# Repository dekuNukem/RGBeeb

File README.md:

# Pimp My Beeb

How I built the **RGBeeb**, a BBC Micro inside a PC case.

With RGB Backlight, USB inputs, ATX PSU, and working full-height floppy drives.

[Click me for a short video!](https://www.youtube.com/watch?v=R9k7dgKrrnE)

## Highlights

* Fully functional BBC Micro inside open-frame ATX PC case

* Animated RGB Backlight

* Working dual full-height 5.25" Floppy Drives

* USB keyboard and gamepad [by USB4VC](https://github.com/dekuNukem/USB4VC/blob/master/README.md)

* ATX power and RGB control [by ATX4VC](https://github.com/dekuNukem/ATX4VC)

## Questions or comments?

Feel free to ask in my [Discord Chatroom](https://discord.gg/T9uuFudg7j), raise a [Github issue](https://github.com/dekuNukem/RGBeeb/issues), or email `dekunukem` `gmail.com`!

## BBC Micro: (A quick) Introduction

* In early 1980s, British Broadcasting Corporation(BBC) started the *Computer Literacy Project*, aiming to introduce people to computers and show what they can do.

* **[Acorn Computer](https://en.wikipedia.org/wiki/Acorn_Computers)**'s design won out, and was developed into **[BBC Microcomputer](https://en.wikipedia.org/wiki/BBC_Micro)**, often nicknamed the "**Beeb**".

* BBC Micro was featured heavily in [TV programmes](https://en.wikipedia.org/wiki/The_Computer_Programme), and became ubiquitous in education environments in UK.

* A common sight in school computer labs, it introduced a whole generation to computing, and inspired many bright minds.

* Acorn went on to develop the **Acorn RISC Machine**, or [ARM](https://en.wikipedia.org/wiki/ARM_architecture_family) in short (Yes, *that* ARM), which are now found in virtually all smartphones, 32-bit microcontrollers, and even desktop PCs.

* It might be relatively unknown outside UK, but BBC Micro holds a significant place in computer history, as well as nostalgia in many peoples hearts!

### Specifications

The original Beeb featured a 6502 microprocessor running at 2MHz, 32K of ROM, and either 16 or 32K of RAM. Its [BASIC interpreter](https://en.wikipedia.org/wiki/BBC_BASIC) was notably one of the fastest of the era, beating even the original IBM PC!

It was also extremely expandable, with a plethora of ports including RS423, cassette, analogue, Econet, a digital user port, a 1MHz bus connection, and a "Tube" expansion slot.

As a result, the Beeb was surprisingly long-lived, lasting more than 10 years. Numerous [upgrades and coprocessors](https://en.wikipedia.org/wiki/BBC_Micro_expansion_unit#ARM_Evaluation_System) were developed, including Z80, 32016, 80186, or even the very first ARM CPU!

## Oh no! You butchered a piece of computer history!

First of all, all modifications here are **non-destructive and reversible**. So no Beebs were harmed during the creation of this project!

What's more, modifying BBC Micros was not unheard of even back then! One great example is the original [Torch Communicator](https://en.wikipedia.org/wiki/Torch_Computers):

A sleek business machine running CP/M with integrated display, keyboard, and disk drives. What's not to like?

At this point, eagle-eyed viewers might notice the UI looks suspiciously familiar! The secret is revealed looking inside the case [thanks to this video](https://www.youtube.com/watch?v=pNdYtTvEAQs):

Yep, they literally nicked the motherboard from a BBC Micro and built their own computer around it!

Despite the humble root, the Torch Communicator was a fairly advanced machine, having a Z80 co-processor running CP/M with networking capabilities, and it was the [first microcomputer](https://nosher.net/archives/computers/micro_decision_1982-05_002) to be fully approved by British Telecom to connect to the telephone and Telex network, in 1982!

Torch Computer went on to develop their [own machines](https://en.wikipedia.org/wiki/Torch_Computers#Torch_Triple_X) later. But this is a great example of building upon an existing computer to expand its capabilities.

## The FrankenBeeb

Of course, Beeb tinkering did not stop at commercial companies, plenty enterprising users had a go as well!

Here are eBay photos of a machine I picked up locally (with authentic 70s carpet):

It's a Beeb with ... a separate keyboard and boxy case??

The top half of the Beeb was replaced with a flat lid. And the keyboard is in its own metal enclosure with a ribbon cable (???).

The new boxy case most likely allow the computer, disk drive and monitor to be stacked on top each other, saving valuable desk space.

A look inside revealed big upgrades, fully kitted out with sidewise expansion card, floppy disc controller, battery backup, a standalone audio jack, and speech synthesis chips. And just look at all the ROMs!

The disc drive contains dual 80 track full height 5.25" floppy drives, with some notes on the door:

There is no brand name or identifying information anywhere on the modifications, which led me to assume that the whole thing was home-made or at least from a kit.

Either way, it looks very professionally done, and is a seriously impressive feat of how far people would go to personalize their computers to their exact liking.

I removed the RIFA caps from the PSU, took lots of photos for documentation, cleaned up the PCB, and tested it out. It actually works! Look at the huge list of ROMs:

The disc drive works too! I decided not to risk the original power supply, and used a modern ATX PSU to power them. The FrankenBeeb read the discs just fine:

As you can see, it's quite a mess indeed. It was at this point that an idea occurred to me:

***Wouldn't it be nice if all those can go into a single ATX PC case?*** 

This way,

* Everything's in one place, cleaner look.

* Interesting juxtaposition between 40-year-old hardware and modern case.

* Very much in the spirit of wacky modding of the era.

* Honestly, why not?

## A Happy Coincidence?

Obviously, the most important part is mounting the motherboard. So I did some measurements.

Imagine my surprise when it turns out the BBC micro motherboard is **almost identical in size** as full-size ATX!

Either it's one hell of a coincidence, or Acorn was so ahead of its time that it predicted ATX form factor by **14 years**!

Still in disbelief, I placed the BBC motherboard inside a ATX case, lo and behold:

It fits almost perfectly! The RGB, cassette, serial, composite and RF ports line up with the I/O window, and there are space for all the connectors in the back! This is almost too good to be true.

Although in this particular case(!!), the PCI bracket is blocking the analogue and econet port, and the long 5.25" drive doesn't go all the way in.

Which brings us neatly to the next part: What case *should* I use?

## Case Selection

Initially, I wanted one of those absolutely obnoxious gaming cases kitted out with RGB straight out of [r/pcmasterrace](https://old.reddit.com/r/pcmasterrace/), just for maximum hilarity. Something [like this:](https://old.reddit.com/r/gamingpc/comments/jb8w25/just_rgb_everything/
)

So I went to look for a case that's:

* Available new

* Full size ATX or larger

* Gaming aesthetics (RGB, Glass panel, etc)

* Has 5.25" bays for two full-height disk drives

It didn't seem like a tall order, but after sifting through dozens of pages on amazon and newegg, I came to the devastating conclusion such case ***simply does not exist anymore***.

As you can see, apparently 5.25" bays just isn't a thing anymore! Instead there is a blank space where it used to be, to the horror of *dozens* of retro modding enthusiasts.

(yes I know there's a case with 2 bays right in that photo, but I need 4 for two drives)

-----

Just when I thought modern cases were a lost cause, I stumbled upon something I completely missed: **open-frame cases**!

Some of them are just scaffolding for mining rigs, but one in particular really caught my eye, the [Thermaltake Core P3 TG Snow](https://uk.thermaltake.com/core-p3-snow-edition.html):

* I really like its striking yet minimalist design, juxtapose neatly with the 1980s technology. It's also a nice break from today's rather bland "gaming black" aesthetics.

* It puts the motherboard on display front-and-center, instead of having to look through a window into a box in conventional cases. Less claustrophobic.

* There are lots of space to work with, and everything is modular. PCI bracket blocking the ports? Simply don't install it!

* And most importantly, the slot cutouts near the front edge are perfect for mounting 5.25" inch drives!

The clean and minimalist design also changed my mind about the overall aesthetics. Instead of full-on obnoxious RGB blast, now I want something more subtle and tasteful. It's still early, so I'll see what I can do.

It's not cheap, but I really liked it, so I ordered one.

## ATX Adapter Plate

I looked up ATX standard, and measured the mounting holes on the BBC motherboard. A simple adapter plate was designed in Inkscape and laser-cut in acrylic.

The case soon arrived, I had the main chassis laid out and tried out the adapter plate:

It works! And already looks pretty good! I really like how modular this case is. 

I then installed the ATX power supply. Annoyingly its RGB fan points downwards, so it is practically invisible with the case standing up. But at least it's white!

## Power to the Beeb

BBC Micro motherboard requires two voltages: +5V and -5V. The former powers all the chips, and the latter only for sound and serial communication.

Fortunately, 5V is readily available on a ATX PSU, and -5V can be derived from -12V with a simple 7905 linear regulator. The PSU itself can be controlled by shorting the green PS_ON signal to ground.

The most basic circuit would be something like this:

One slight issue is that I want to use the power button on the PC case, which is momentary. That means I can't just hook it up to the PS_ON pin, as it will only turn on while the button is held down.

I thought about using a simple flip-flop to toggle the PWR_ON signal with button presses, and it quickly got out of hand. How about putting it on a PCB? What about button debouncing? I can put the 7905 on there too! Might as well break out ALL the voltages! A fan header would be useful! What about RGB?

## Enter ATX4VC

In the end, I decided to go all out and design a controller specifically for using **ATX power supply on retro computers**, amply named **[ATX4VC](https://github.com/dekuNukem/ATX4VC/blob/master/README.md)**:

It combines many convenient features in one place:

* All common voltages: +12V, +5V, +3.3V, -5V, -12V. Fused.

* Power button and power LED headers

* Two 4-pin PWM fan headers

* Two Addressable RGB (ARGB) headers

* USB-C power output

[Click me for learn more / buy one / user manual](https://github.com/dekuNukem/ATX4VC/blob/master/README.md)

Altogether, it's an all-in-one package for replacing old unreliable (and sometime explosive!) power supplies with modern ATX PSUs, with provision for cooling and aesthetic upgrades.

--------

It also fits neatly in a 2.5 inch drive bay, I hooked up the power button and LED headers, as well as a fan, and pressed the button.

It works! PSU turns on, fan spins and lights up, and voltage rails are live.

We still need to connect it to the motherboard though, which will come later.

## Did anyone say RGB?

I do want to involve some RGB in this build, usually they come from RGB fans, RAM sticks, or light strips, none of which are really suitable here:

* Beeb doesn't need fan cooling, and it's a bit silly to add them just for looks.

* Same with RGB RAM sticks

* I can try light strips, but they tend to be a bit tacky, and hard to conceal in open-frame cases

So all in all, the RGB situation wasn't looking too hot. However, I did find something much better!

----

Ground planes and large copper pours really didn't become popular until late 80s, which means the earlier circuit boards are basically translucent. If you shine a light from behind, it will illuminate the delicate and intricate design of all the traces on the PCB.

And here, I want to expand the idea by **adding RGB backlight behind the entire motherboard**, it would require a lot of LEDs, but if it looks good, it's worth the trouble in my book.

For mockup, I stuck some RGB light strips on the acrylic plate, and hastily wired them together.

Seeing it for the first time, I was in awe.

What a sight to behold! And this is just a solid white, should be even more striking with animations and more colours.

I could have just used that, but it was rather messy, so I designed a whole new custom PCB with evenly distributed RGB LEDs, that also function as the ATX adapter plate. I also left a hole in the middle so cables can exit underneath and not block the light. 

I used **USB-C** to carry the ARGB signal. Often used for charging, it is already designed to carry decent amount of current. A single cable plugs directly into ATX4VC, much cleaner this way.

This is the biggest PCB I have ever designed, it is not very complicated, but did take me a while to solder all 168 LEDs by hand. Fortunately, everything worked on first try, and it gets blindingly bright when turned all the way up!

How does it look like with the motherboard? Well:

Now **that's** what you call R, G, and B!

## USB on BBC

With power and RGB sorted, what's the next must-have item on a modern PC?

Why yes, **USB keyboard, mouse, and gamepads** of course! With such a modern case, it's only natural that I use it with modern inputs!

As if by total coincidence, I happen to have a project for *exactly that*! What are the odds?

[USB4VC](https://github.com/dekuNukem/USB4VC/blob/master/README.md) let you **use USB keyboard, mouse, and gamepads on retro computers**, as an alternative to rare, expensive, and unreliable proprietary vintage peripherals.

With a modular design, different computers are supported by swapping out **Protocol Cards**.

Naturally, I made one for the Beeb, with connectors for keyboard, joystick, and AMX user port mouse.

The prototype has a few bodge wires, but they are fixed in the latest revision. And it works!

Pretty fun using a wireless keyboard and Xbox controller on the Beeb!

And if for some reason you literally can't even be bothered to *type*, you can always let [duckyPad](https://github.com/dekuNukem/duckyPad/blob/master/README.md) do it!

duckyPad is a hot-swap mechanical macropad that helps speed up workflow by automating actions using duckyScript.

Read more about [USB4VC](https://github.com/dekuNukem/USB4VC/blob/master/README.md) and [duckyPad](https://github.com/dekuNukem/duckyPad/blob/master/README.md) if you're interested!

------

Phew! Two plugs in a row! Really pushing it there! 😅

## Here comes the twist

With a flurry of modern upgrades, time to balance it out with some good ol' 5.25" drives!

I wanted to have them from the start, partly for contrast with all the new stuff, and partly because I actually have a huge pile of floppies that I want to explore.

I picked two drives, a 48TPI Tandon TM-100-2A from an OG IBM PC, and a 96TPI Shugart SA460 from the FrankenBeeb.

With both 40 and 80 tracks, it should cover most of the floppies from the era.

After some trail and error, I found that the cable needs to have **no twists**, and drive ID set manually with jumper.

I had to manually de-twist my cable by cutting and re-soldering the wires in order, which was a bit annoying, but with that and manually setting the drive ID 0 and 1, both worked!

With Intel 8271 disk controller and Acorn DFS, two sides of a floppy appear as two separate drives. So the Shugart is drive 0 and 2, and Tandon is drive 1 and 3. This disk seem to have Elite and some save data on it, very nice!

With the setup working, I now have to figure out how to mount them on the case.

The right side of the case has slots for mounting water cooling radiators, I went to local hardware store and bought some metal brackets that's roughly the size, and cut them to length and drilled holes in them.

They are fastened into the slot and hold the drives from the bottom. I really wanted something more substantial, like a one-piece metal bracket, but custom fabrication would have been a lot more expensive.

Anyway, I test-mounted the drives, and they look pretty good! The face plates line up with the front of the case.

Everything seemed to be going suspiciously well, but of course, things soon went back to normal when I tried to install the motherboard:

The connectors in the back are too long! They are touching the floppy cable, preventing the motherboard from being installed.

Well, it's about time that we do something to it...

## Motherboard modifications

This is the part where I put the motherboard under the knife (well, soldering iron). As mentioned before, all modifications are purely for aesthetic reasons, and are totally **optional and reversible**.

First, I desoldered the Tube, 1MHz, and user port header:

That was NOT easy, experience and extra care is needed to not lift any pads or damage the PCB.

Next, out comes the keyboard connector and all 7 power connector blades:

I then soldered a straight header on the user port, so I can use the excellent MMFS SD card adapter.

(I think I put it in backwards in this photo, make sure to double check!)

I then ran power cables to connect all the rails together, 5V, GND, and -5V.

If making your own, make sure the cable is thick enough to carry at least 2A of current. Double check for shorts between 5V and GND, and the exposed conductor is not touching nearby traces and components.

I also soldered the keyboard header on the back side.

## Putting it all together

Time to finally put everything together! 

I fed the floppy and power cable through the hole in the adapter plate, and mounted the motherboard.

In the back, I:

* Cable tied the USB4VC in place, and connected the ribbon cable.

* Installed two 9-Pin USB header to USB-A adapters, so USB devices can be plugged in on the front panel.

* Cable tied the speaker near the front of the case.

* Powered USB4VC with a USB-C cable.

I then connected up ATX4VC:

* Power rails on top.

* Two USB-C power output on left, one for USB4VC, one for RGB backlight plate.

* Case power button and power LED on right. Case reset button used to change RGB mode.

* ATX motherboard connector on the bottom.

It controls power, lighting and cooling of the whole system. I really like how clean and integrated this is, much better than a nest of flying wires and components.

I then installed the floppy drives, and gave it a test:

It still works! This motherboard is an issue 4, I picked it because most chips are socketed (including all RAMs), making it very easy to test and troubleshoot. The solder mask also seems thinner as well, allowing more light to pass through.

I decked it out with optional upgrades for the big day, with disk controller, speech synthesis, ADC, and econet. Annoyingly the econet chip itself is missing, and I'll need to get one.

Anyway, time to install the tempered glass for the money shot:

## Conclusion

It's amazing how quickly a simple idea can get out of hand, I started out just wanting to put a BBC Micro motherboard into a PC case, and in the end I developed a new protocol card for [USB4VC](https://github.com/dekuNukem/USB4VC/blob/master/README.md), an [ATX power controller](https://github.com/dekuNukem/ATX4VC/blob/master/README.md) just for retro computers, and a custom RGB backlight plate with 168 LEDs. Go big or go home, right? 😅

None of this is totally necessary, but just like the Torch Communicator and the FrankenBeeb, the whole ordeal of dragging it kicking and screaming into the RGB age made it feel more special, and I guess this is what modification is all about.

Of course, I omitted a lot of less glamorous stuff such as writing and debugging firmwares, waiting for parts, many hardware revisions (ATX4VC had 6!), and fixing up old motherboards themselves. Took me about 3 months from start to finish.

Still, I learned a lot about the history and clever design of this machine, and made something that hopefully benefits the community at large. With everything put together, it looks every bit as good as i imagined from the beginning.

As for what's next, I might add a Torch Z80 card for CP/M capability, but to be honest, I spent so much time building this thing, I haven't had much time actually using it! Guess I'm going to fix that.

## Questions and answers

### I want to build one!

Sure! As usual the project is open-source, and all you really need is the ATX adapter plate, which [can be found here](https://github.com/dekuNukem/RGBeeb/tree/master/plates).

Just give the files to a lase-cut acrylic manufacturer. The rest is up to you! Hopefully reading this article gave you some ideas.

### Can I buy one?

(Mostly) No.

This is a very custom build with parts that can be unreliable and difficult to source, so I'm not inclined to turn it into a business.

I'm not completely closed to the idea of making a few one-offs though, but it would need to be worth my while one way or the other.

[Get in touch](#get-in-touch) if you want to have a discussion or have any questions.

### Is BBC Micro Protocol Card available?

Might be, but not at the moment.

BBC Micro already has built-in keyboard, so I don't see much demand for it. Also the firmware needs a little more polish to meet my public release standards.

So again, [let me know](#get-in-touch) if you want it, I'll update in the Discord channel.

## Other Fun Stuff

I've done a few other fun projects over the years, feel free to check them out:

[duckyPad: Do-It-All Mechanical Macropad](https://github.com/dekuNukem/duckypad/blob/master/README.md): A 15-key mechanical macropad with hot-swap, RGB, and sophisticated multi-line scripting.

[ATX4VC](https://github.com/dekuNukem/ATX4VC/blob/master/README.md): Replace vintage computer power supplies with ATX PSU!

[USB4VC](https://github.com/dekuNukem/USB4VC/blob/master/README.md): USB Inputs on Retro Computers

[Pimp My Microwave](https://github.com/dekuNukem/pimp_my_microwave/blob/master/README.md): Fixing my microwave by grafting an RGB mechanical keyboard

[Daytripper: Hide-my-windows Laser Tripwire](https://github.com/dekuNukem/daytripper/blob/master/README.md): Saves the day while you slack off!

[Bob Rewinder](https://github.com/dekuNukem/bob_cassette_rewinder/blob/master/README.md): Hacking Detergent DRM for 98% Cost Saving

[From Aduino to STM32](https://github.com/dekuNukem/STM32_tutorials/blob/master/README.md): A detailed tutorial to get you started with STM32 development.

[List of all my repos](https://github.com/dekuNukem?tab=repositories)

## Get in touch

Questions or comments? Feel free to ask in official [ATX4VC Chatroom](https://discord.gg/T9uuFudg7j), raise a [Github issue](https://github.com/dekuNukem/RGBeeb/issues), or email `dekunukem` `gmail.com`!

## Extra Trivia

Congrats for reaching the bottom! If you stuck around this long, I can only post a few more interesting stuff!

Remember the FrankenBeeb? I actually got *another* BBC Micro from the same person that's also customized. Take a look:

The owl logo from drilled holes! It looked very professionally done. Spacing is even, drill is clean, and they even deburred every single hole!

I have no idea if this was a one-off DIY job or some kind of send-in modification that people could do. Let me know what you think!

Also, notice the keyboard, some keys are actually from a Torch Communicator!

The blue keys, and the tiny "exact space" key, which I have no idea what it's for. Is regular space bar not exact enough?

--------

Eagle eyed viewers might also notice quite a few different motherboards in the photos. There's a Issue 3, a Issue 7, and two Issue 4s.

I must have like half a dozen Beeb motherboards, and just kept swapping part around to keep them going! I used the Issue 4 board in the end because it has all the optional upgrades.

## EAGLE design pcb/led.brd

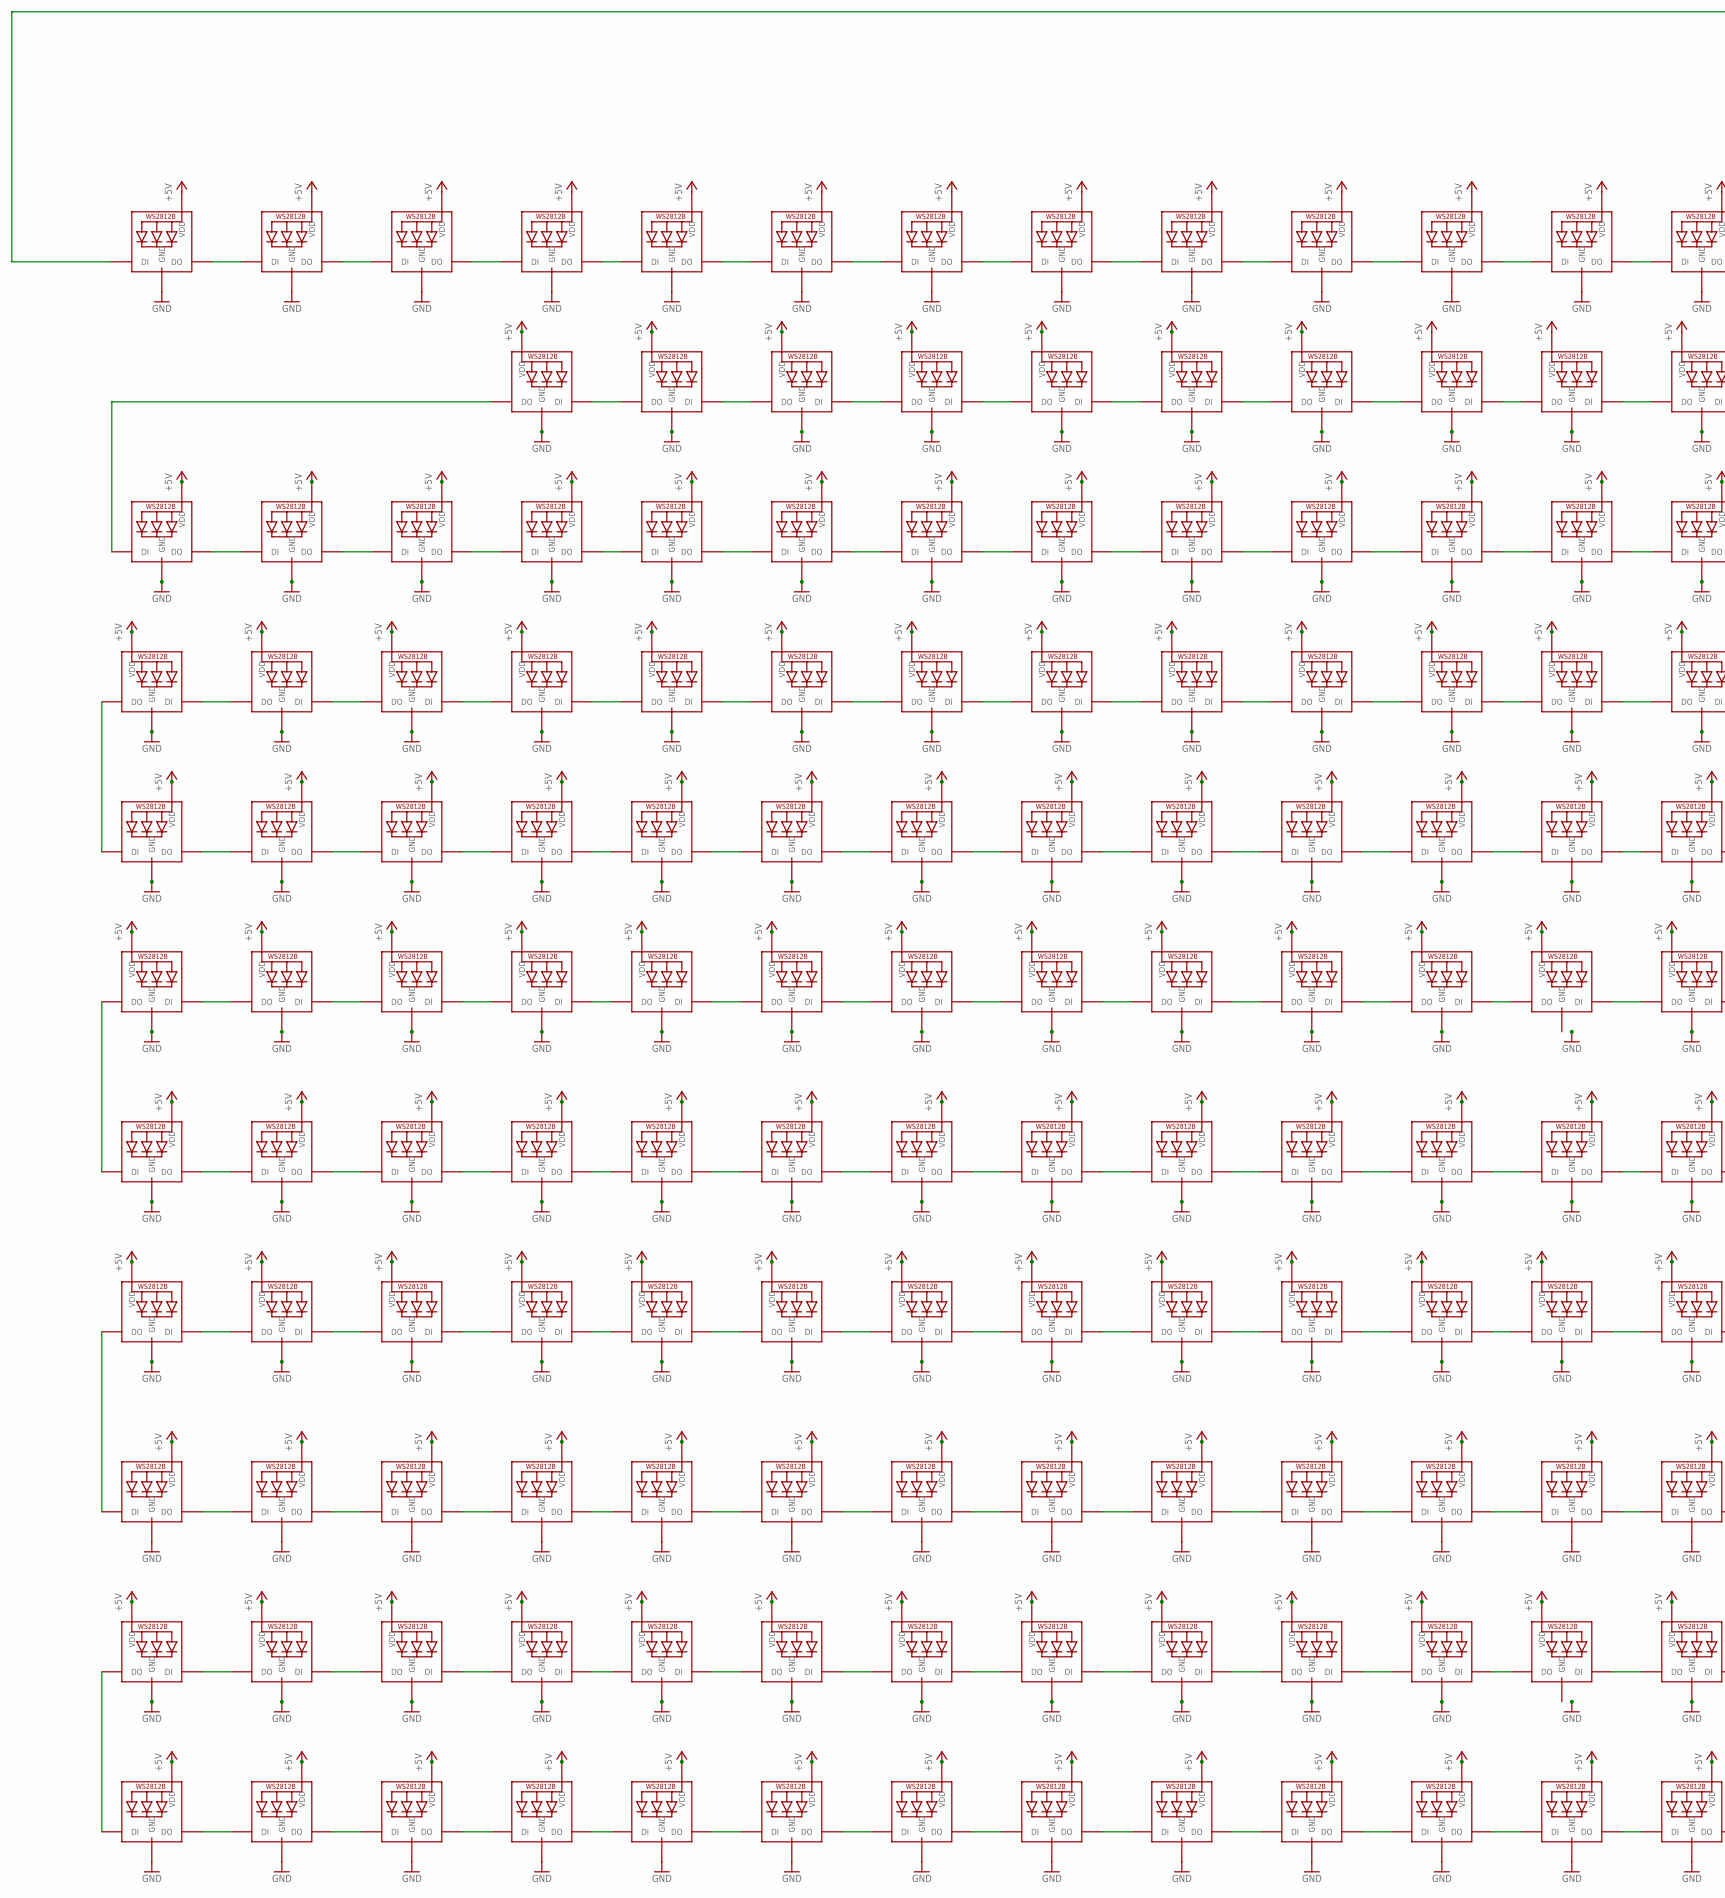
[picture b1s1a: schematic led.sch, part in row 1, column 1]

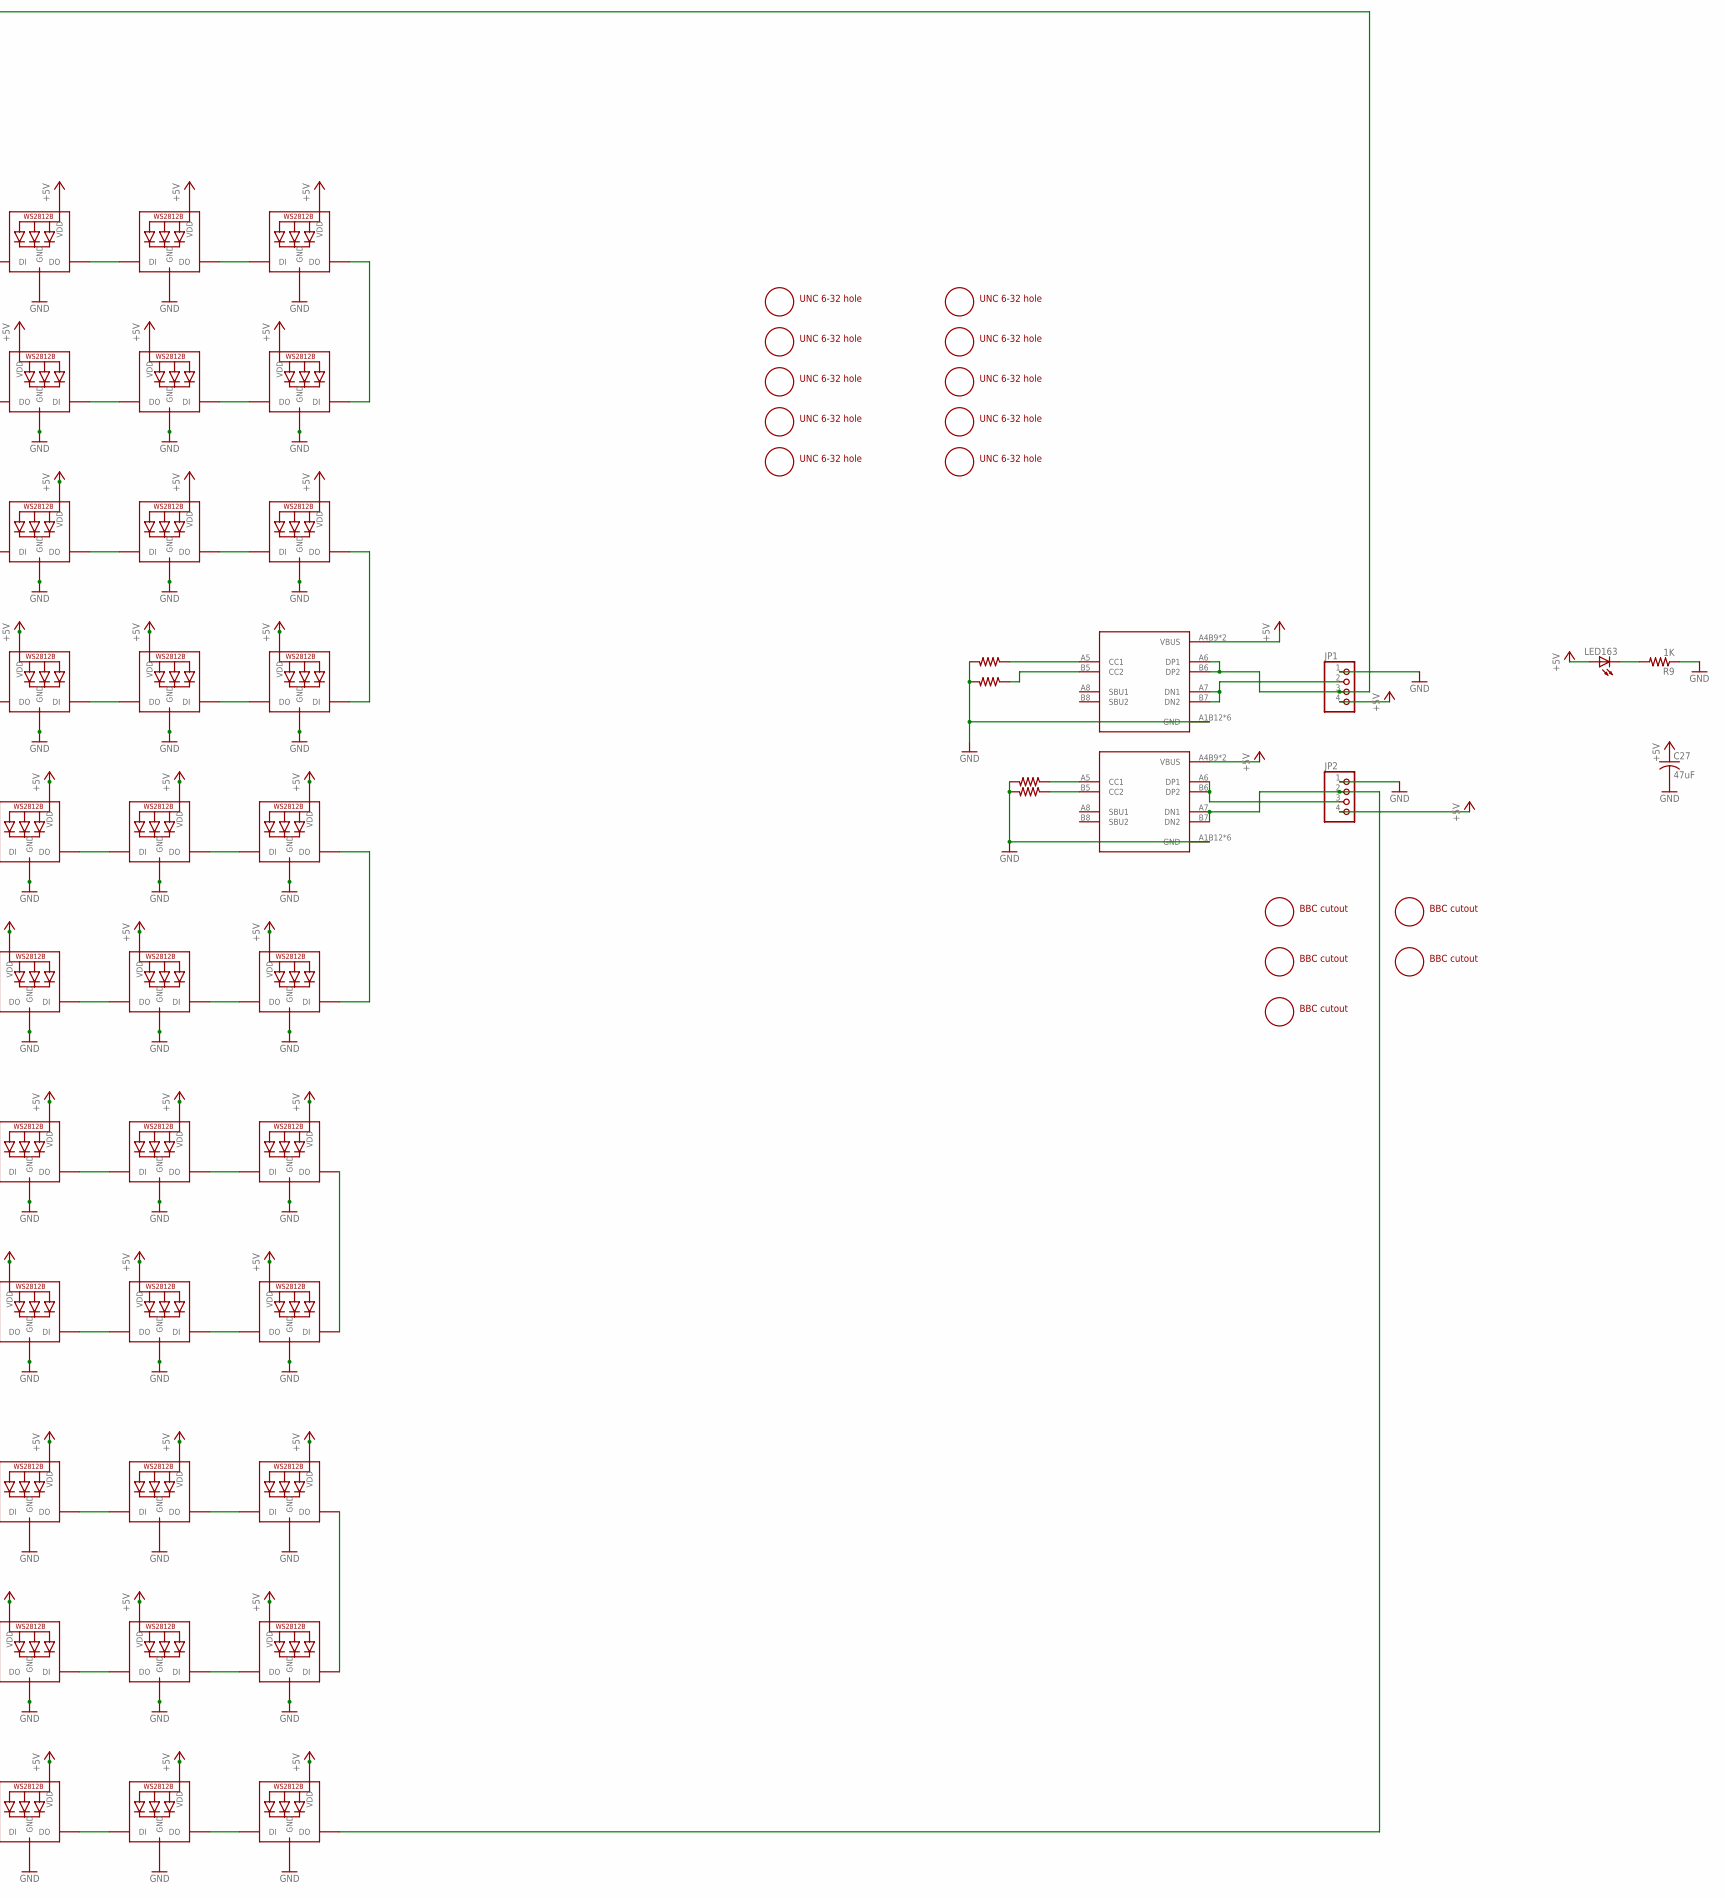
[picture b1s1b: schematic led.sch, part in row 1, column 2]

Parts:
C27: 47uF; C1210
JP1, JP2: PINHD-1X4; 1X04
LED1, LED2, LED3, LED4, LED5, LED6, LED7, LED8, LED9, LED10, LED11, LED12, LED13, LED14, LED15, LED16, LED17, LED18, LED19, LED20, LED21, LED22, LED23, LED24, LED25, LED26, LED27, LED28, LED29, LED30, LED31, LED32, LED33, LED34, LED35, LED36, LED37, LED38, LED39, LED40, LED41, LED42, LED43, LED44, LED45, LED46, LED47, LED48, LED49, LED50, LED51, LED52, LED53, LED54, LED55, LED56, LED57, LED58, LED59, LED60, LED61, LED62, LED63, LED64, LED65, LED66, LED67, LED68, LED69, LED70, LED71, LED72, LED73, LED74, LED75, LED76, LED77, LED78, LED79, LED80, LED81, LED82, LED83, LED84, LED85, LED86, LED87, LED88, LED89, LED90, LED91, LED92, LED93, LED94, LED95, LED96, LED97, LED98, LED99, LED100, LED101, LED102, LED103, LED104, LED105, LED106, LED107, LED108, LED109, LED110, LED111, LED112, LED113, LED114, LED115, LED116, LED117, LED118, LED119, LED120, LED121, LED122, LED123, LED124, LED125, LED126, LED127, LED128, LED129, LED130, LED131, LED132, LED133, LED134, LED135, LED136, LED137, LED138, LED139, LED140, LED141, LED142, LED143, LED144, LED145, LED146, LED147, LED148, LED149, LED150, LED151, LED152, LED153, LED154, LED155, LED156, LED157, LED158, LED159, LED160, LED161, LED162: WS2812B; REVERSE_MNT
LED163: LEDCHIP-LED0805; CHIP-LED0805
R1, R2, R3, R4: 5.1K; 0805
R9: 1K; 0805
U1, U2: USBC_16P; USBC_16P_FOOT
U$1, U$2, U$3, U$4, U$5, U$6, U$7, U$8, U$9, U$10: MOTHERBOARD_MOUNTING_HOLE; MOTEHRBOARD_MOUNTING_HOLE
U$11, U$12, U$13, U$14, U$15: BBC_CUTOUT; BBC_MOUNTING_HOLE_CUTOUT

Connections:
+5V: C27.1, JP1.4, JP2.4, LED1.VDD, LED2.VDD, LED3.VDD, LED4.VDD, LED5.VDD, LED6.VDD, LED7.VDD, LED8.VDD, LED9.VDD, LED10.VDD, LED11.VDD, LED12.VDD, LED13.VDD, LED14.VDD, LED15.VDD, LED16.VDD, LED17.VDD, LED18.VDD, LED19.VDD, LED20.VDD, LED21.VDD, LED22.VDD, LED23.VDD, LED24.VDD, LED25.VDD, LED26.VDD, LED27.VDD, LED28.VDD, LED29.VDD, LED30.VDD, LED31.VDD, LED32.VDD, LED33.VDD, LED34.VDD, LED35.VDD, LED36.VDD, LED37.VDD, LED38.VDD, LED39.VDD, LED40.VDD, LED41.VDD, LED42.VDD, LED43.VDD, LED44.VDD, LED45.VDD, LED46.VDD, LED47.VDD, LED48.VDD, LED49.VDD, LED50.VDD, LED51.VDD, LED52.VDD, LED53.VDD, LED54.VDD, LED55.VDD, LED56.VDD, LED57.VDD, LED58.VDD, LED59.VDD, LED60.VDD, LED61.VDD, LED62.VDD, LED63.VDD, LED64.VDD, LED65.VDD, LED66.VDD, LED67.VDD, LED68.VDD, LED69.VDD, LED70.VDD, LED71.VDD, LED72.VDD, LED73.VDD, LED74.VDD, LED75.VDD, LED76.VDD, LED77.VDD, LED78.VDD, LED79.VDD, LED80.VDD, LED81.VDD, LED82.VDD, LED83.VDD, LED84.VDD, LED85.VDD, LED86.VDD, LED87.VDD, LED88.VDD, LED89.VDD, LED90.VDD, LED91.VDD, LED92.VDD, LED93.VDD, LED94.VDD, LED95.VDD, LED96.VDD, LED97.VDD, LED98.VDD, LED99.VDD, LED100.VDD, LED101.VDD, LED102.VDD, LED103.VDD, LED104.VDD, LED105.VDD, LED106.VDD, LED107.VDD, LED108.VDD, LED109.VDD, LED110.VDD, LED111.VDD, LED112.VDD, LED113.VDD, LED114.VDD, LED115.VDD, LED116.VDD, LED117.VDD, LED118.VDD, LED119.VDD, LED120.VDD, LED121.VDD, LED122.VDD, LED123.VDD, LED124.VDD, LED125.VDD, LED126.VDD, LED127.VDD, LED128.VDD, LED129.VDD, LED130.VDD, LED131.VDD, LED132.VDD, LED133.VDD, LED134.VDD, LED135.VDD, LED136.VDD, LED137.VDD, LED138.VDD, LED139.VDD, LED140.VDD, LED141.VDD, LED142.VDD, LED143.VDD, LED144.VDD, LED145.VDD, LED146.VDD, LED147.VDD, LED148.VDD, LED149.VDD, LED150.VDD, LED151.VDD, LED152.VDD, LED153.VDD, LED154.VDD, LED155.VDD, LED156.VDD, LED157.VDD, LED158.VDD, LED159.VDD, LED160.VDD, LED161.VDD, LED162.VDD, LED163.A, U1.A4B9 (VBUS), U1.B4A9 (VBUS), U2.A4B9 (VBUS), U2.B4A9 (VBUS)
GND: C27.2, JP1.1, JP2.1, LED1.GND, LED2.GND, LED3.GND, LED4.GND, LED5.GND, LED6.GND, LED7.GND, LED8.GND, LED9.GND, LED10.GND, LED11.GND, LED12.GND, LED13.GND, LED14.GND, LED15.GND, LED16.GND, LED17.GND, LED18.GND, LED19.GND, LED20.GND, LED21.GND, LED22.GND, LED23.GND, LED24.GND, LED25.GND, LED26.GND, LED27.GND, LED28.GND, LED29.GND, LED30.GND, LED31.GND, LED32.GND, LED33.GND, LED34.GND, LED35.GND, LED36.GND, LED37.GND, LED38.GND, LED39.GND, LED40.GND, LED41.GND, LED42.GND, LED43.GND, LED44.GND, LED45.GND, LED46.GND, LED47.GND, LED48.GND, LED49.GND, LED50.GND, LED51.GND, LED52.GND, LED53.GND, LED54.GND, LED55.GND, LED56.GND, LED57.GND, LED58.GND, LED59.GND, LED60.GND, LED61.GND, LED62.GND, LED63.GND, LED64.GND, LED65.GND, LED66.GND, LED67.GND, LED68.GND, LED69.GND, LED70.GND, LED71.GND, LED72.GND, LED73.GND, LED74.GND, LED75.GND, LED76.GND, LED77.GND, LED78.GND, LED79.GND, LED80.GND, LED81.GND, LED82.GND, LED83.GND, LED84.GND, LED85.GND, LED86.GND, LED87.GND, LED88.GND, LED89.GND, LED90.GND, LED91.GND, LED92.GND, LED93.GND, LED94.GND, LED95.GND, LED96.GND, LED97.GND, LED98.GND, LED99.GND, LED100.GND, LED101.GND, LED102.GND, LED103.GND, LED104.GND, LED105.GND, LED106.GND, LED107.GND, LED108.GND, LED109.GND, LED110.GND, LED111.GND, LED112.GND, LED113.GND, LED114.GND, LED115.GND, LED116.GND, LED117.GND, LED118.GND, LED119.GND, LED120.GND, LED121.GND, LED122.GND, LED123.GND, LED124.GND, LED125.GND, LED126.GND, LED127.GND, LED128.GND, LED129.GND, LED130.GND, LED131.GND, LED132.GND, LED133.GND, LED134.GND, LED135.GND, LED136.GND, LED137.GND, LED138.GND, LED139.GND, LED140.GND, LED141.GND, LED142.GND, LED143.GND, LED144.GND, LED145.GND, LED146.GND, LED147.GND, LED148.GND, LED149.GND, LED150.GND, LED151.GND, LED152.GND, LED153.GND, LED154.GND, LED155.GND, LED156.GND, LED157.GND, LED158.GND, LED159.GND, LED160.GND, LED161.GND, LED162.GND, R1.2, R2.2, R3.2, R4.2, R9.1, U1.A1B12 (GND), U1.B11A12 (GND), U1.P$13 (GND), U1.P$14 (GND), U1.P$15 (GND), U1.P$16 (GND), U2.A1B12 (GND), U2.B11A12 (GND), U2.P$13 (GND), U2.P$14 (GND), U2.P$15 (GND), U2.P$16 (GND)
unnamed: LED1.DOUT (DO), LED2.DIN (DI)
unnamed: LED2.DOUT (DO), LED3.DIN (DI)
unnamed: LED3.DOUT (DO), LED4.DIN (DI)
unnamed: LED4.DOUT (DO), LED5.DIN (DI)
unnamed: LED5.DOUT (DO), LED6.DIN (DI)
unnamed: LED6.DOUT (DO), LED7.DIN (DI)
unnamed: R3.1, U1.A5 (CC1)
unnamed: LED8.DOUT (DO), LED9.DIN (DI)
unnamed: LED9.DOUT (DO), LED10.DIN (DI)
unnamed: LED10.DOUT (DO), LED11.DIN (DI)
unnamed: LED11.DOUT (DO), LED12.DIN (DI)
unnamed: LED12.DOUT (DO), LED13.DIN (DI)
unnamed: LED13.DOUT (DO), LED14.DIN (DI)
unnamed: LED14.DOUT (DO), LED15.DIN (DI)
unnamed: LED15.DOUT (DO), LED16.DIN (DI)
unnamed: LED16.DOUT (DO), LED17.DIN (DI)
unnamed: LED17.DOUT (DO), LED18.DIN (DI)
unnamed: LED18.DOUT (DO), LED19.DIN (DI)
unnamed: LED19.DOUT (DO), LED20.DIN (DI)
unnamed: LED20.DOUT (DO), LED21.DIN (DI)
unnamed: LED21.DOUT (DO), LED22.DIN (DI)
unnamed: LED22.DOUT (DO), LED23.DIN (DI)
unnamed: LED23.DOUT (DO), LED24.DIN (DI)
unnamed: LED24.DOUT (DO), LED25.DIN (DI)
unnamed: LED25.DOUT (DO), LED26.DIN (DI)
unnamed: LED26.DOUT (DO), LED27.DIN (DI)
unnamed: LED28.DOUT (DO), LED29.DIN (DI)
unnamed: LED29.DOUT (DO), LED30.DIN (DI)
unnamed: LED30.DOUT (DO), LED31.DIN (DI)
unnamed: LED31.DOUT (DO), LED32.DIN (DI)
unnamed: R1.1, U2.B5 (CC2)
unnamed: LED32.DOUT (DO), LED33.DIN (DI)
unnamed: R2.1, U2.A5 (CC1)
unnamed: LED33.DOUT (DO), LED34.DIN (DI)
unnamed: LED34.DOUT (DO), LED35.DIN (DI)
unnamed: LED35.DOUT (DO), LED36.DIN (DI)
unnamed: LED36.DOUT (DO), LED37.DIN (DI)
unnamed: LED37.DOUT (DO), LED38.DIN (DI)
unnamed: LED38.DOUT (DO), LED39.DIN (DI)
unnamed: LED39.DOUT (DO), LED40.DIN (DI)
unnamed: LED40.DOUT (DO), LED41.DIN (DI)
unnamed: LED41.DOUT (DO), LED42.DIN (DI)
unnamed: LED42.DOUT (DO), LED43.DIN (DI)
unnamed: LED27.DOUT (DO), LED28.DIN (DI)
unnamed: LED54.DOUT (DO), LED55.DIN (DI)
unnamed: LED43.DOUT (DO), LED44.DIN (DI)
unnamed: LED44.DOUT (DO), LED45.DIN (DI)
unnamed: LED45.DOUT (DO), LED46.DIN (DI)
unnamed: LED46.DOUT (DO), LED47.DIN (DI)
unnamed: LED47.DOUT (DO), LED48.DIN (DI)
unnamed: LED48.DOUT (DO), LED49.DIN (DI)
unnamed: LED49.DOUT (DO), LED50.DIN (DI)
unnamed: LED50.DOUT (DO), LED51.DIN (DI)
unnamed: LED51.DOUT (DO), LED52.DIN (DI)
unnamed: LED52.DOUT (DO), LED53.DIN (DI)
unnamed: LED53.DOUT (DO), LED54.DIN (DI)
unnamed: LED55.DOUT (DO), LED56.DIN (DI)
unnamed: LED56.DOUT (DO), LED57.DIN (DI)
unnamed: LED58.DOUT (DO), LED59.DIN (DI)
unnamed: LED59.DOUT (DO), LED60.DIN (DI)
unnamed: LED60.DOUT (DO), LED61.DIN (DI)
unnamed: LED61.DOUT (DO), LED62.DIN (DI)
unnamed: LED62.DOUT (DO), LED63.DIN (DI)
unnamed: LED63.DOUT (DO), LED64.DIN (DI)
unnamed: LED64.DOUT (DO), LED65.DIN (DI)
unnamed: LED65.DOUT (DO), LED66.DIN (DI)
unnamed: LED66.DOUT (DO), LED67.DIN (DI)
unnamed: LED67.DOUT (DO), LED68.DIN (DI)
unnamed: LED68.DOUT (DO), LED69.DIN (DI)
unnamed: LED69.DOUT (DO), LED70.DIN (DI)
unnamed: LED70.DOUT (DO), LED71.DIN (DI)
unnamed: LED71.DOUT (DO), LED72.DIN (DI)
unnamed: LED57.DOUT (DO), LED58.DIN (DI)
unnamed: LED73.DOUT (DO), LED74.DIN (DI)
unnamed: LED74.DOUT (DO), LED75.DIN (DI)
unnamed: LED75.DOUT (DO), LED76.DIN (DI)
unnamed: LED76.DOUT (DO), LED77.DIN (DI)
unnamed: LED77.DOUT (DO), LED78.DIN (DI)
unnamed: LED78.DOUT (DO), LED79.DIN (DI)
unnamed: LED79.DOUT (DO), LED80.DIN (DI)
unnamed: LED80.DOUT (DO), LED81.DIN (DI)
unnamed: LED81.DOUT (DO), LED82.DIN (DI)
unnamed: LED82.DOUT (DO), LED83.DIN (DI)
unnamed: LED83.DOUT (DO), LED84.DIN (DI)
unnamed: LED84.DOUT (DO), LED85.DIN (DI)
unnamed: LED85.DOUT (DO), LED86.DIN (DI)
unnamed: LED86.DOUT (DO), LED87.DIN (DI)
unnamed: LED72.DOUT (DO), LED73.DIN (DI)
unnamed: LED88.DOUT (DO), LED89.DIN (DI)
unnamed: LED89.DOUT (DO), LED90.DIN (DI)
unnamed: LED90.DOUT (DO), LED91.DIN (DI)
unnamed: LED91.DOUT (DO), LED92.DIN (DI)
unnamed: LED92.DOUT (DO), LED93.DIN (DI)
unnamed: LED93.DOUT (DO), LED94.DIN (DI)
unnamed: LED94.DOUT (DO), LED95.DIN (DI)
unnamed: LED95.DOUT (DO), LED96.DIN (DI)
unnamed: LED96.DOUT (DO), LED97.DIN (DI)
unnamed: LED97.DOUT (DO), LED98.DIN (DI)
unnamed: LED98.DOUT (DO), LED99.DIN (DI)
unnamed: LED99.DOUT (DO), LED100.DIN (DI)
unnamed: LED100.DOUT (DO), LED101.DIN (DI)
unnamed: LED101.DOUT (DO), LED102.DIN (DI)
unnamed: LED87.DOUT (DO), LED88.DIN (DI)
unnamed: LED103.DOUT (DO), LED104.DIN (DI)
unnamed: LED104.DOUT (DO), LED105.DIN (DI)
unnamed: LED105.DOUT (DO), LED106.DIN (DI)
unnamed: LED106.DOUT (DO), LED107.DIN (DI)
unnamed: LED107.DOUT (DO), LED108.DIN (DI)
unnamed: LED108.DOUT (DO), LED109.DIN (DI)
unnamed: LED109.DOUT (DO), LED110.DIN (DI)
unnamed: LED110.DOUT (DO), LED111.DIN (DI)
unnamed: LED111.DOUT (DO), LED112.DIN (DI)
unnamed: LED112.DOUT (DO), LED113.DIN (DI)
unnamed: LED113.DOUT (DO), LED114.DIN (DI)
unnamed: LED114.DOUT (DO), LED115.DIN (DI)
unnamed: LED115.DOUT (DO), LED116.DIN (DI)
unnamed: LED116.DOUT (DO), LED117.DIN (DI)
unnamed: LED102.DOUT (DO), LED103.DIN (DI)
unnamed: LED118.DOUT (DO), LED119.DIN (DI)
unnamed: LED119.DOUT (DO), LED120.DIN (DI)
unnamed: LED120.DOUT (DO), LED121.DIN (DI)
unnamed: LED121.DOUT (DO), LED122.DIN (DI)
unnamed: LED122.DOUT (DO), LED123.DIN (DI)
unnamed: LED123.DOUT (DO), LED124.DIN (DI)
unnamed: LED124.DOUT (DO), LED125.DIN (DI)
unnamed: LED125.DOUT (DO), LED126.DIN (DI)
unnamed: LED126.DOUT (DO), LED127.DIN (DI)
unnamed: LED127.DOUT (DO), LED128.DIN (DI)
unnamed: LED128.DOUT (DO), LED129.DIN (DI)
unnamed: LED129.DOUT (DO), LED130.DIN (DI)
unnamed: LED130.DOUT (DO), LED131.DIN (DI)
unnamed: LED131.DOUT (DO), LED132.DIN (DI)
unnamed: LED117.DOUT (DO), LED118.DIN (DI)
unnamed: LED133.DOUT (DO), LED134.DIN (DI)
unnamed: LED134.DOUT (DO), LED135.DIN (DI)
unnamed: LED135.DOUT (DO), LED136.DIN (DI)
unnamed: LED136.DOUT (DO), LED137.DIN (DI)
unnamed: LED137.DOUT (DO), LED138.DIN (DI)
unnamed: LED138.DOUT (DO), LED139.DIN (DI)
unnamed: LED139.DOUT (DO), LED140.DIN (DI)
unnamed: LED140.DOUT (DO), LED141.DIN (DI)
unnamed: LED141.DOUT (DO), LED142.DIN (DI)
unnamed: LED142.DOUT (DO), LED143.DIN (DI)
unnamed: LED143.DOUT (DO), LED144.DIN (DI)
unnamed: LED144.DOUT (DO), LED145.DIN (DI)
unnamed: LED145.DOUT (DO), LED146.DIN (DI)
unnamed: LED146.DOUT (DO), LED147.DIN (DI)
unnamed: LED132.DOUT (DO), LED133.DIN (DI)
unnamed: LED148.DOUT (DO), LED149.DIN (DI)
unnamed: LED149.DOUT (DO), LED150.DIN (DI)
unnamed: LED150.DOUT (DO), LED151.DIN (DI)
unnamed: LED151.DOUT (DO), LED152.DIN (DI)
unnamed: LED152.DOUT (DO), LED153.DIN (DI)
unnamed: LED153.DOUT (DO), LED154.DIN (DI)
unnamed: LED154.DOUT (DO), LED155.DIN (DI)
unnamed: LED155.DOUT (DO), LED156.DIN (DI)
unnamed: LED156.DOUT (DO), LED157.DIN (DI)
unnamed: LED157.DOUT (DO), LED158.DIN (DI)
unnamed: LED158.DOUT (DO), LED159.DIN (DI)
unnamed: LED159.DOUT (DO), LED160.DIN (DI)
unnamed: LED160.DOUT (DO), LED161.DIN (DI)
unnamed: LED161.DOUT (DO), LED162.DIN (DI)
unnamed: LED147.DOUT (DO), LED148.DIN (DI)
unnamed: R4.1, U1.B5 (CC2)
unnamed: JP1.3, LED1.DIN (DI), U2.A6 (DP1), U2.B6 (DP2)
unnamed: JP1.2, U2.A7 (DN1), U2.B7 (DN2)
unnamed: JP2.3, U1.A6 (DP1), U1.B6 (DP2)
unnamed: JP2.2, LED162.DOUT (DO), U1.A7 (DN1), U1.B7 (DN2)
unnamed: LED7.DOUT (DO), LED8.DIN (DI)
unnamed: LED163.C, R9.2

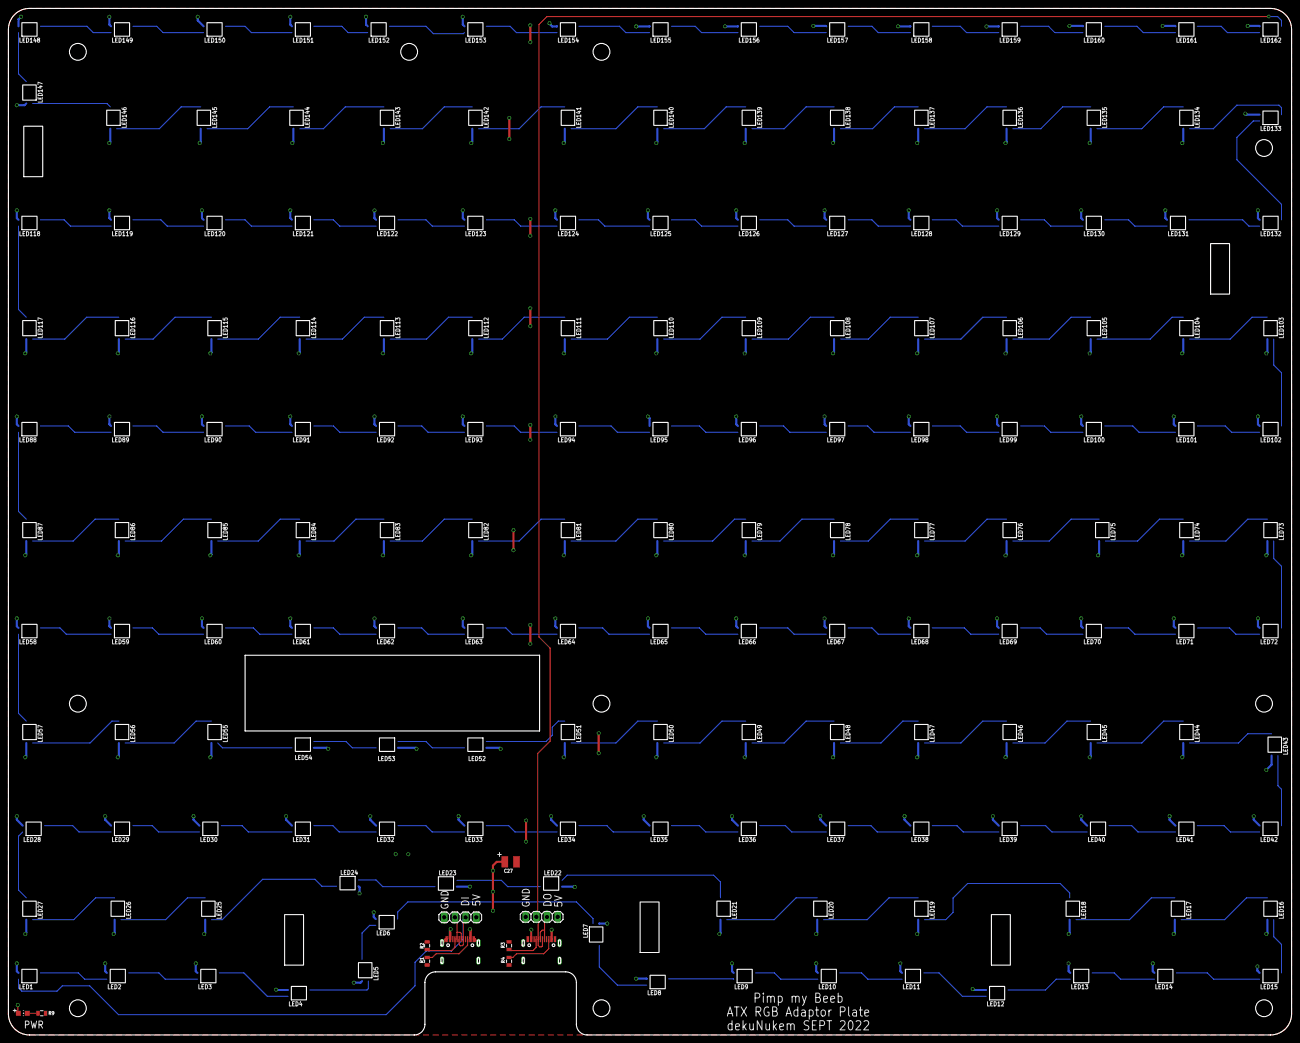
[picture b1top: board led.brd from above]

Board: 2 copper layers, 305.0 x 244.0 mm, 188 parts (0 on the bottom side), 172 nets.

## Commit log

2022-09-03 added files
2022-09-03 just dumping ideas into writing
2022-09-04 more idea dumps
2022-09-04 trying to get digital pot working
2022-09-12 added more schematics
2022-09-18 fleshing out README
2022-09-19 writing README
2022-09-19 working on README
2022-09-19 still wirting
2022-09-20 still writign
2022-09-20 added new comparison
2022-09-25 still writing
2022-09-27 added osborne
2022-09-28 updated photo
2022-09-28 added more photos
2022-09-29 more photos
2022-09-29 adding photos
2022-10-01 add more photos
2022-10-02 writing
2022-10-05 should be ready now
2022-10-05 fixed a few typos
2022-10-05 removed unused file
2022-10-06 updated acrylic plates
2022-10-06 fix typo
2022-10-06 fixed typo, mentioned missing -5V rail
2022-10-06 added a bit of trivia
2022-10-06 fix typos

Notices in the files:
parts and their libraries:
SparkFun-Passives: Licensing: Creative Commons ShareAlike 4.0 International - https://creativecommons.org/licenses/by-sa/4.0
